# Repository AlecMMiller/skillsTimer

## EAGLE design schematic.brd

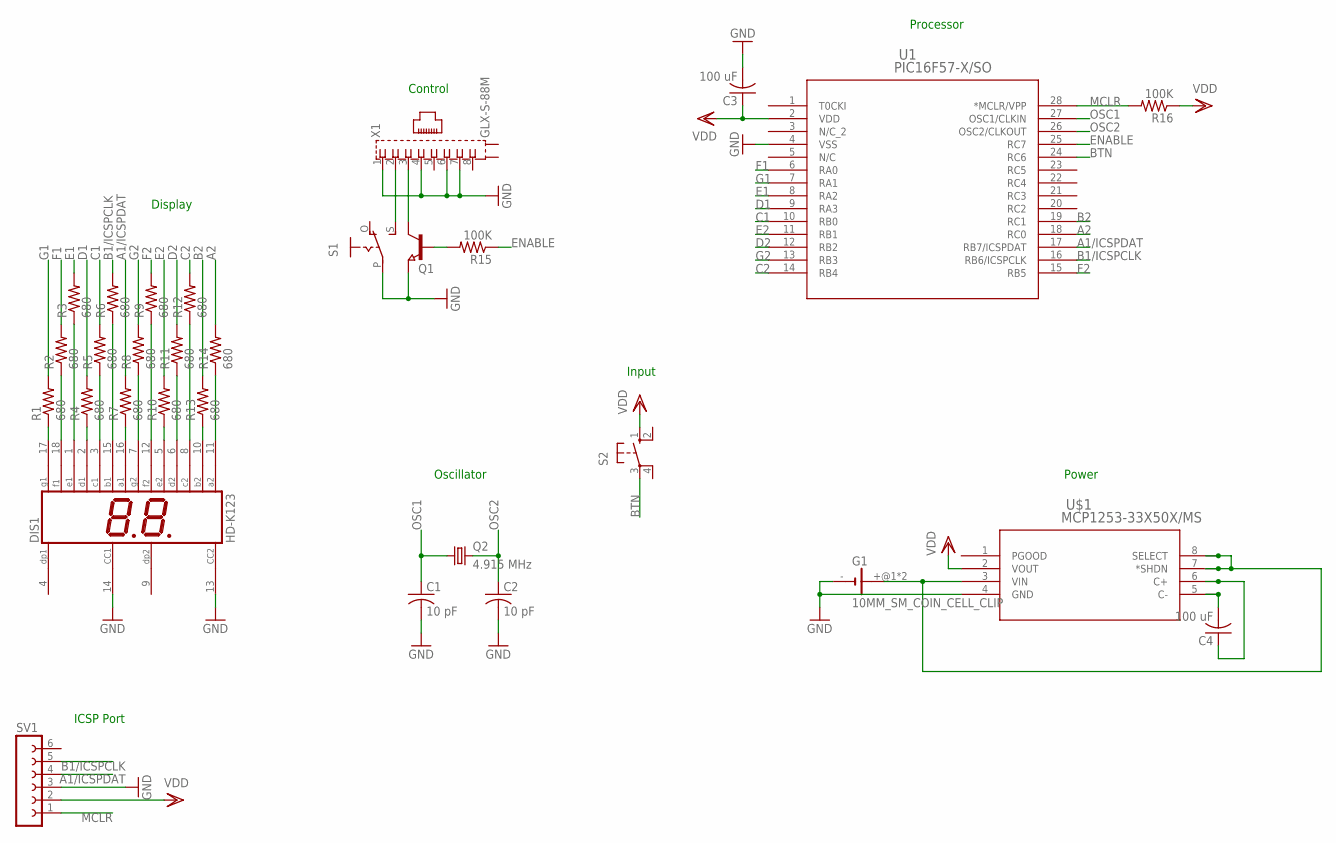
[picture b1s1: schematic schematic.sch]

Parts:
C1, C2: 10 pF; C0603
C3, C4: 100 uF; C0603
DIS1: HD-K123; HDSP-R
G1: 10MM_SM_COIN_CELL_CLIP
Q1: NPN-TRANSISTOR_SOT23; SOT23
Q2: 4.915 MHz; SM49
R1, R2, R3, R4, R5, R6, R7, R8, R9, R10, R11, R12, R13, R14: 680; R0603
R15, R16: 100K; R0603
S1: EG1218S; EG1218
S2: 40-XX; B3F-40XX
SV1: FE06-1; FE06
U1: PIC16F57-X/SO; SOIC28-W_MC
U$1: MCP1253-33X50X/MS; MSOP8_MC
X1: GLX-S-88M

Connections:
A1/ICSPDAT: R7.2, SV1.4, U1.17 (RB7/ICSPDAT)
A2: R14.2, U1.18 (RC0)
B1/ICSPCLK: R6.2, SV1.5, U1.16 (RB6/ICSPCLK)
B2: R13.2, U1.19 (RC1)
BTN: S2.3, U1.24 (RC6)
C1: R5.2, U1.10 (RB0)
C2: R12.2, U1.14 (RB4)
D1: R4.2, U1.9 (RA3)
D2: R11.2, U1.12 (RB2)
E1: R3.2, U1.8 (RA2)
E2: R10.2, U1.11 (RB1)
ENABLE: R15.1, U1.25 (RC7)
F1: R2.2, U1.6 (RA0)
F2: R9.2, U1.15 (RB5)
G1: R1.2, U1.7 (RA1)
G2: R8.2, U1.13 (RB3)
GND: C1.2, C2.2, C3.2, DIS1.13 (CC2), DIS1.14 (CC1), G1.-, Q1.2 (E), S1.P, SV1.3, U1.4 (VSS), U$1.4 (GND), X1.1, X1.4, X1.6, X1.7
MCLR: R16.2, SV1.1, U1.28 (*MCLR/VPP)
unnamed: G1.+@1 (+), G1.+@2 (+), U$1.3 (VIN), U$1.7 (*SHDN), U$1.8 (SELECT)
unnamed: DIS1.15 (B1), R6.1
unnamed: DIS1.3 (C1), R5.1
unnamed: DIS1.2 (D1), R4.1
unnamed: DIS1.1 (E1), R3.1
unnamed: DIS1.18 (F1), R2.1
unnamed: DIS1.17 (G1), R1.1
unnamed: DIS1.16 (A1), R7.1
unnamed: DIS1.7 (G2), R8.1
unnamed: DIS1.12 (F2), R9.1
unnamed: DIS1.5 (E2), R10.1
unnamed: DIS1.6 (D2), R11.1
unnamed: DIS1.8 (C2), R12.1
unnamed: DIS1.10 (B2), R13.1
unnamed: DIS1.11 (A2), R14.1
unnamed: C4.2, U$1.5 (C-)
unnamed: C4.1, U$1.6 (C+)
unnamed: S1.S, X1.2
unnamed: Q1.1 (B), R15.2
unnamed: Q1.3 (C), X1.3
OSC1: C1.1, Q2.1, U1.27 (OSC1/CLKIN)
OSC2: C2.1, Q2.2, U1.26 (OSC2/CLKOUT)
VDD: C3.1, R16.1, S2.1 (S), SV1.2, U1.2 (VDD), U$1.2 (VOUT)

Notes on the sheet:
Display
Control
Oscillator
ICSP Port
Input
Processor
Power

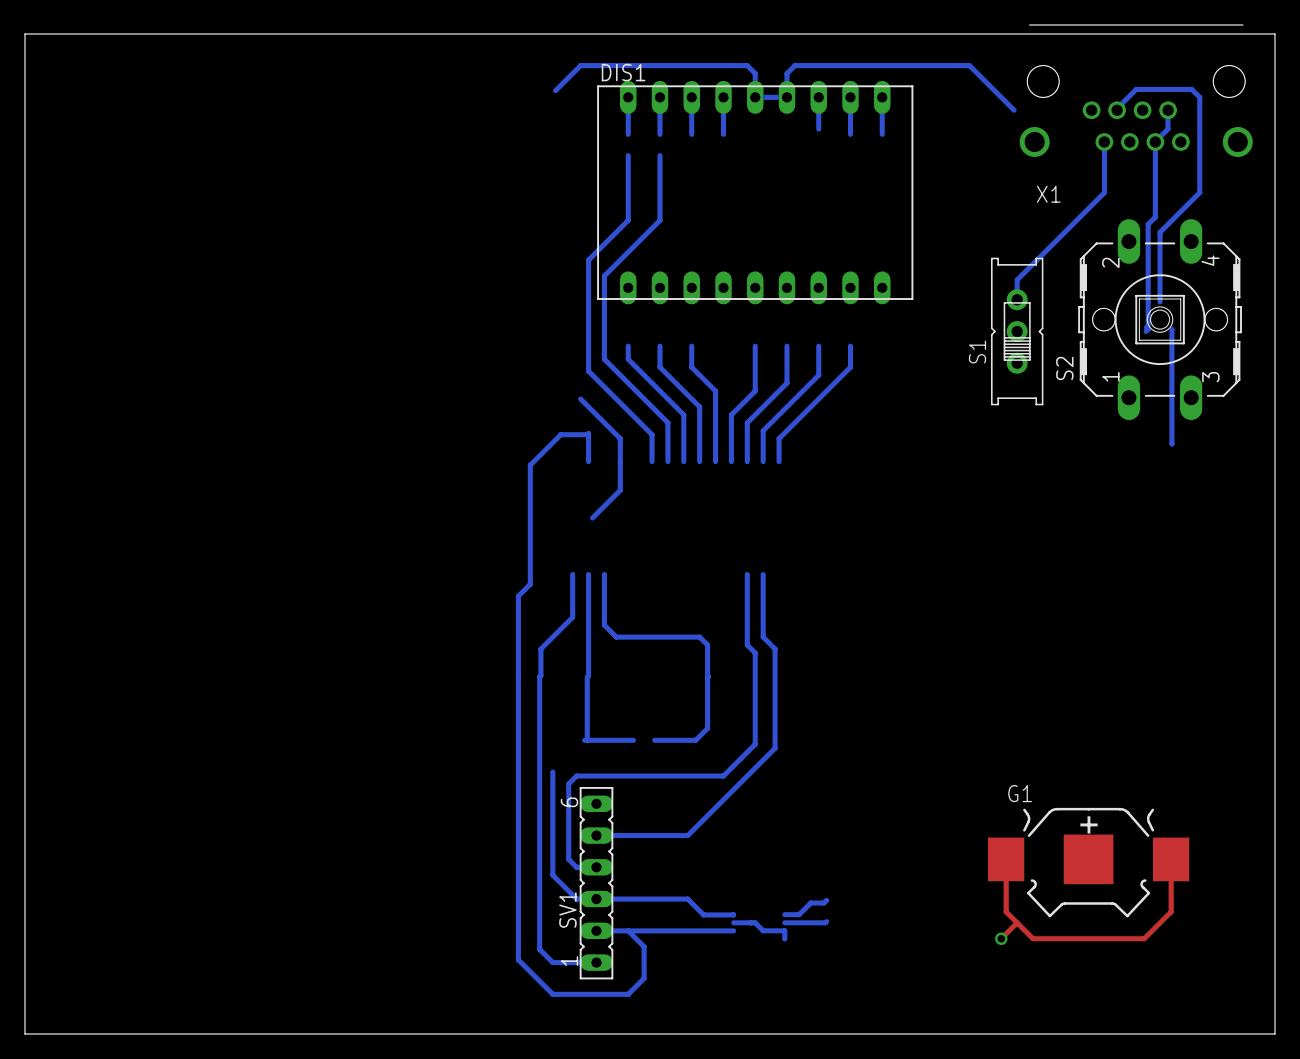
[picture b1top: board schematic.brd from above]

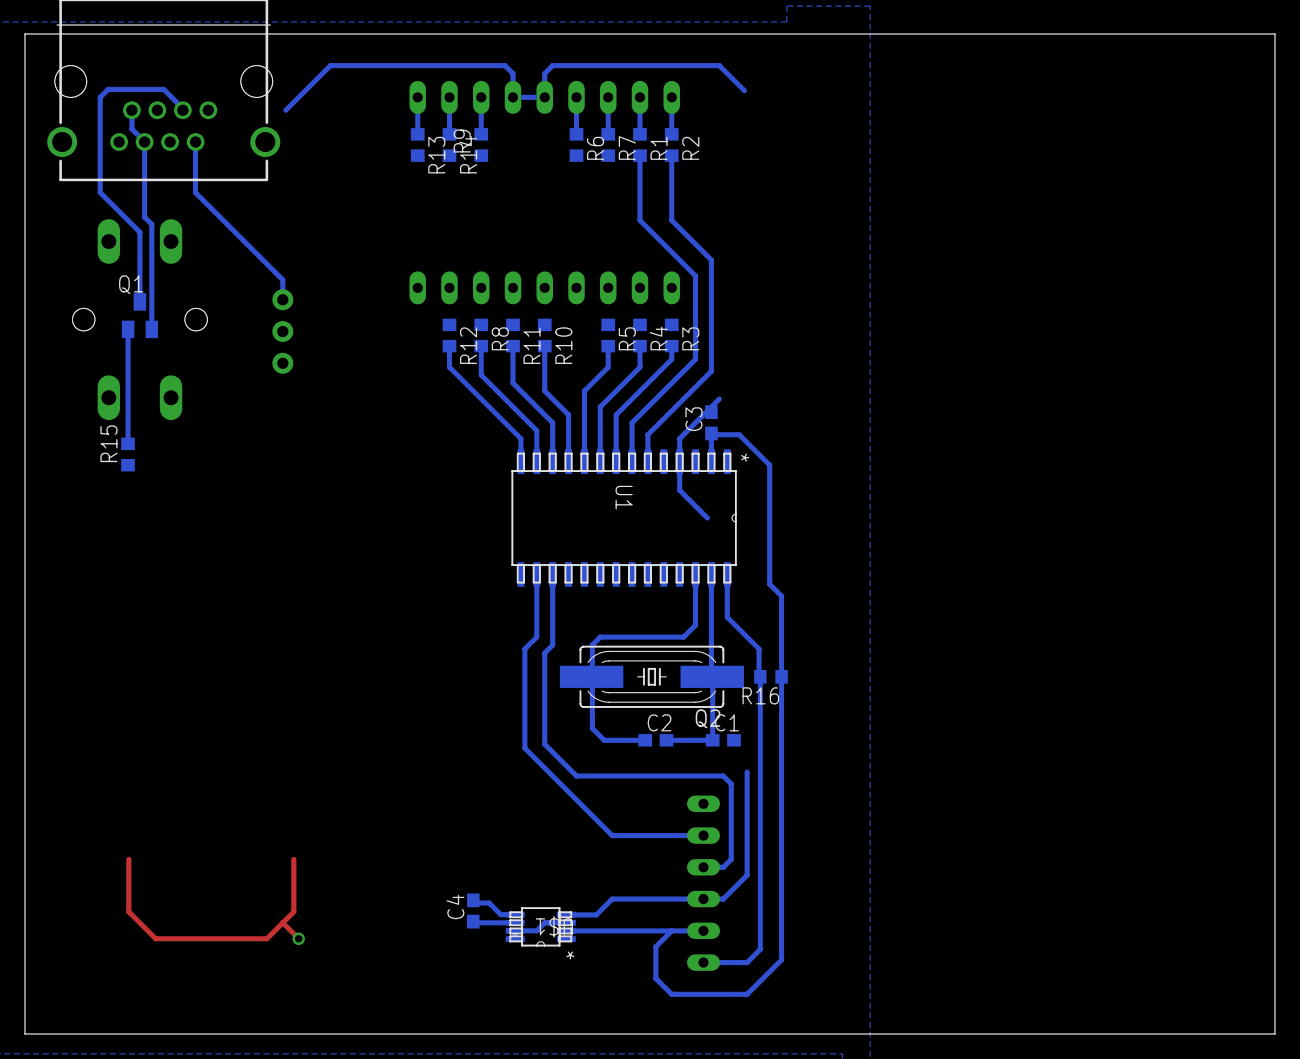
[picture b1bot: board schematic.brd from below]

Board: 2 copper layers, 100.0 x 80.7 mm, 30 parts (24 on the bottom side), 41 nets.

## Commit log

2015-07-30 Initial commit of skills timer
